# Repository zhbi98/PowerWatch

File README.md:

# PowerWatch 迷你 USB 电源功率计

## 1. 项目简介

PowerWatch 是我设计的一个 Mini-USB 电源功率计，设计包含外观结构，电路 PCB，程序固件。

PowerWatch 在硬件设计上支持同时采样被测电源的电压，电流及功率等参数，同时通过软件的形式实现了电能实时监测功能。

电能实时监测功能可以方便的知道被监测电源所输出的电能。 比如通过 PowerWatch 可以知道充电宝为手机充电时，充电宝流入手机的电能为多少 mAh。

而其中 mAh 表明的是电能单位，例如以 $x$ mA 电流持续输出 $1$ h 时间，则输出的电能为 $x$ mAh。

## 2. 硬件介绍

**(1)** 微控制器：采用国产兆易 GD32F103RCT6，芯片主频 96MHz 最高可达 108MHz，64P 引脚，RAM 空间 64KB，ROM 空间 256KB，支持 USB 通信。

**(2)** 屏幕：驱动芯片 ST7789V3，材质 IPS，采用 8 位并行 8080 通信接口，分辨率 320x170。

**(3)** Flash 芯片：GD25Q64 64MBit 即 8MByte。

**(4)** 电压电流采样芯片：采用德州仪器 TI 的 INA226AIDGSR 芯片。 

**(5)** 外壳模型：3D 打印，材料使用尼龙或工程塑料 。

## 3. 目录说明

### 3.1 Firmware 目录

该目录包含 PowerWatch 的所有功能源码实现，芯片驱动库，以及 Keil 编译工程所在目录，现在来简单介绍一下。

`mdk5/` 目录即为 MDK-ARM（即 Keil5 集成开发环境） 的工程文件。

`test/` 目录包含所有功能实现源码，以及需要用到的芯片驱动库，图形界面库 LVGL。

程序主要包含以下内容：

**(1)** GD32f103 的 USB Device 设备驱动，USB 驱动使用的设备描述符是 CDC 虚拟串口，使用 USB 接口可以用于和上位机进行数据通讯。

**(2)** ST7789V3 屏幕芯片驱动。

**(3)** 电压电流采样芯片驱动。

**(4)** 移植好的 LVGL8.2.0 的 UI 绘图库，这个 UI 库可以实现美观的图形界面，使用 LVGL 后就不需要我们自己控制屏幕逐像素的绘制图形来实现 UI 了。

注意：如果需要编译此工程需要安装 keil5 集成开发环境，以及在 keil5 中安装 GD32F10 系列的芯片描述包, 安装好后点击本项目工程文件夹下的工程文件启动 keil 直接编译即可。

GD32F10 芯片描述包可以到兆易官方网站下载，找到 **GD32F1x0 AddOn** 压缩包，芯片描述包就在该压缩包下，下载地址：[点击这里](https://www.gd32mcu.com/cn/download/7?kw=GD32F1)。

---

power_watch_firmware_v1.0.hex：为 PowerWatch 源码的编译后的固件，如果使用编译固件，需要使芯片进入 BOOT 模式，并使用 PCB 板上预留的串口来写入该固件。

### 3.2 Hardware 目录

PowerWatch 的 PCB 工程源文件，该文件夹下包含电路原理图，以及 PCB 制造文件（即 Gerber 文件），器件 BOM 单（用于 SMT 贴片），器件位置文件（用于 SMT 贴片）。

将 Gerber 文件压缩后到嘉立创网站下单即可将 PCB 打样出来，BOM 单和器件位置文件是嘉立创格式，PCB 打样后可以自行按照 BOM 单购买元器件手工焊接，或利用我提供的 BOM 单和器件坐标文件运用嘉立创的 SMT 贴片服务来贴片。

硬件 PCB 已经打样验证通过，想制作的小伙伴可以放心打样使用。

---

PCB 设计时原本的设想是使用 **STM32F103RCT6** 这颗芯片作为微控制器使用的，但是奈何 **STM32F103RCT6** 价格较高，所以最终芯片使用的是国产兆易的 **GD32F103RCT6** 系列芯片。

但是这对电路并不影响，因为 **GD32F103RCT6** 可以不需要任何改动而实现 PIN 对 PIN 的引脚以及外设兼容 **STM32F103RCT6** 芯片（即它们的每一根引脚和外设的功能是相同的）。

### 3.3 Image 目录

该目录是功率计制作实物效果图片展示，观看制作效果可以查看该目录下的实物照片。

### 3.4 Structure 目录

该目录存放功率计外壳模型文件 `.step` 格式，外壳模型包含壳体，按键帽，屏幕支架，上盖板，直接下载用于 3D 打印即可。

为了美观考虑盖板最好使用透明亚克力板进行制作，普通 3D 打印无法实现透明。

**(1)** 壳体 box_v2.0.step 建议采用黑色尼龙材材料 3D 打印。

**(2)** 屏幕支架 bracket_v2.0.step 建议采用透明树脂材料 3D 打印。

**(3)** 上盖板 panel_v2.0.step 建议采用亚克力或聚碳酸酯材料 CNC 加工。

**(4)** 按键帽 button1_v2.0.step，button2_v2.0.step，button3_v2.0.step，button4_v2.0.step 建议采用尼龙材料 3D 打印。

### 3.5 Docs 目录

用到的芯片配套的数据手册。

## 4. 外观设计

**最初的 V1.0 版本模型效果**

**改进后 V2.0 版本模型效果**

## 5. 实物展示

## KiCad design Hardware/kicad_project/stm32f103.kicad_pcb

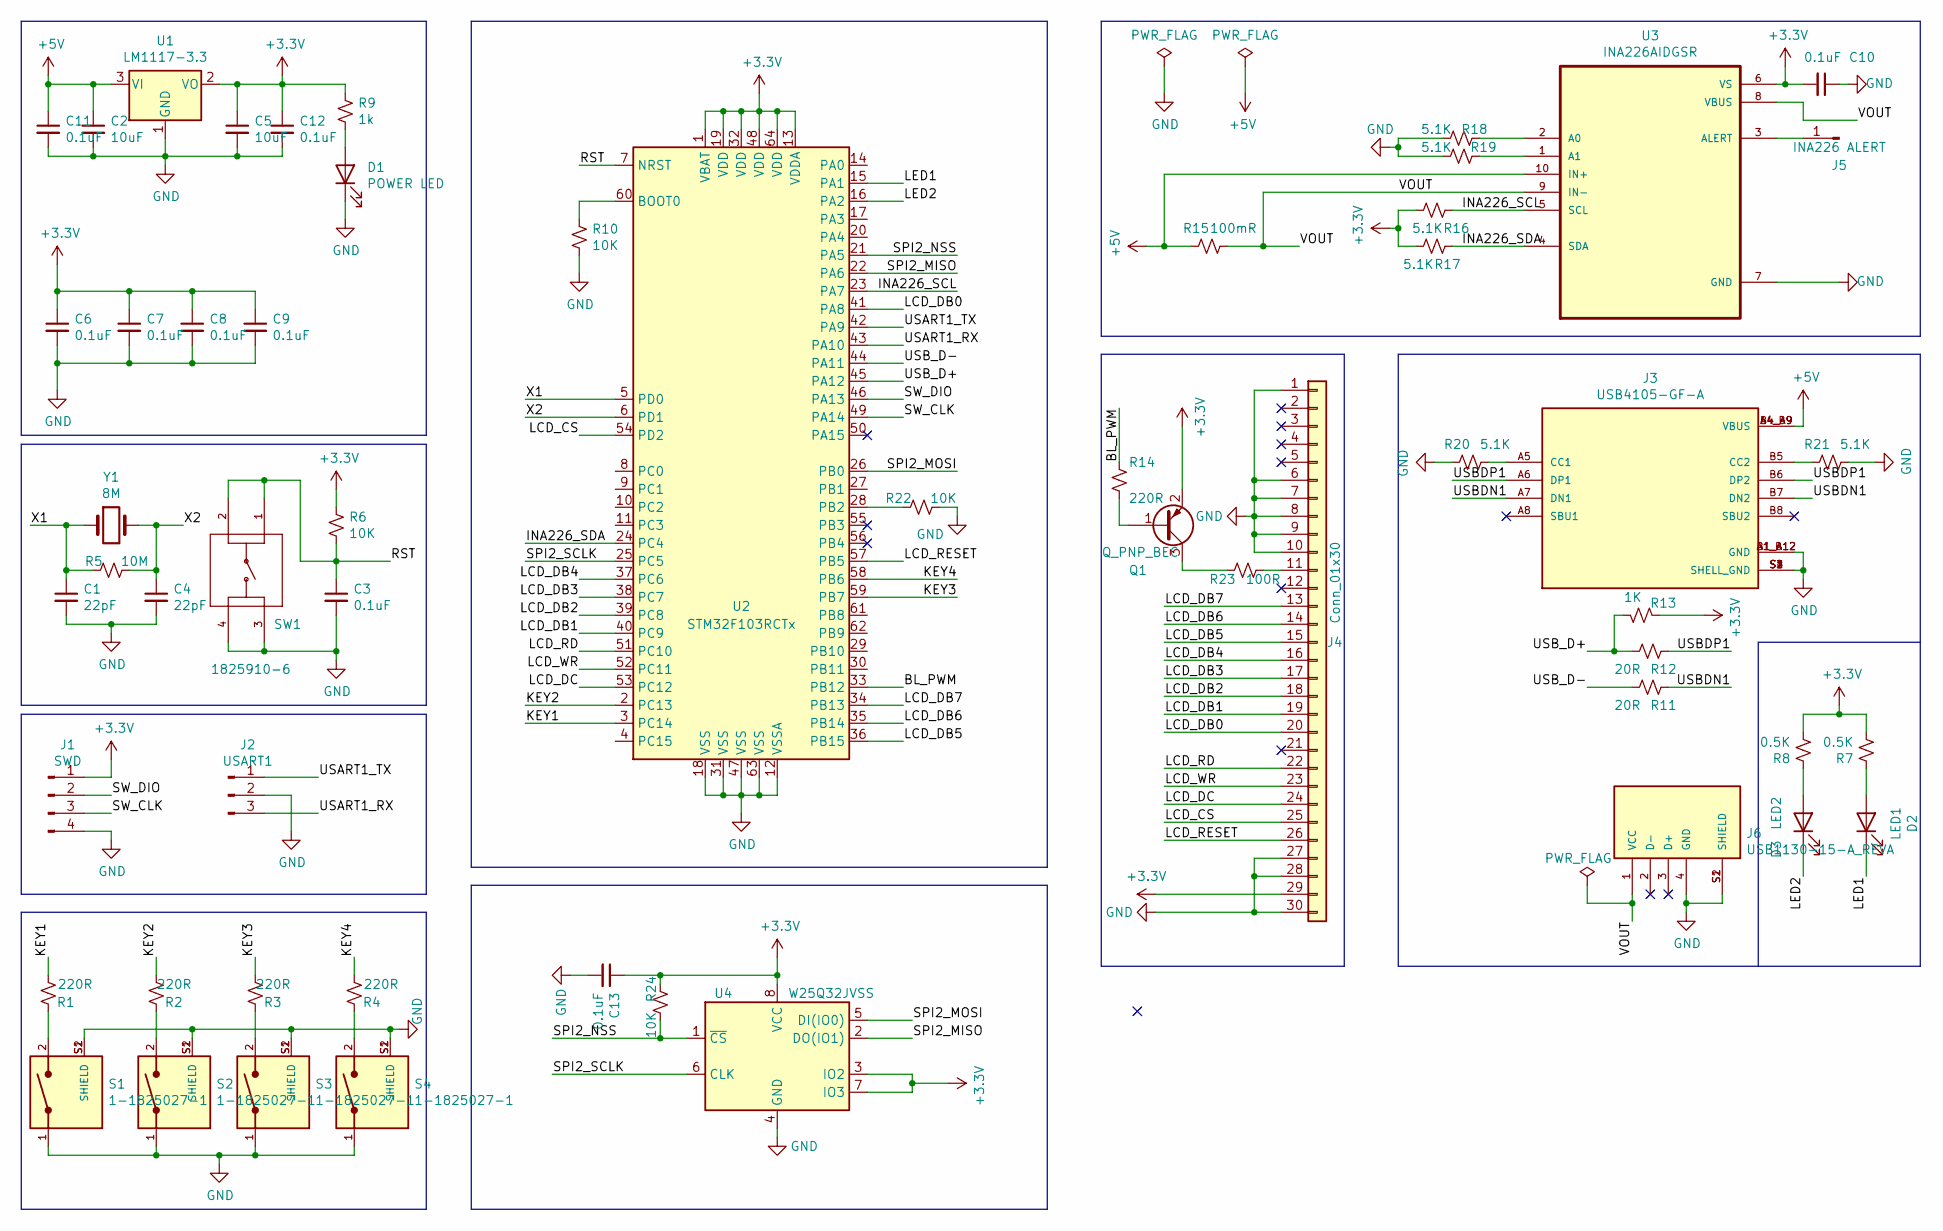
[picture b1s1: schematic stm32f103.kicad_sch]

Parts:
C1, C4: 22pF; C_0805_2012Metric
C2, C5: 10uF; C_0805_2012Metric
C3, C6, C7, C8, C9, C10, C11, C12, C13: 0.1uF; C_0805_2012Metric
D1: POWER LED; LED_0805_2012Metric
D2: LED1; LED_0805_2012Metric
D3: LED2; LED_0805_2012Metric
J1: SWD; PinSocket_1x04_P2.54mm_Vertical
J2: USART1; PinSocket_1x03_P2.54mm_Vertical
J3: USB4105-GF-A; USB-C-SMD_16P_USB4105-GF-A; PARTREV A3
J4: Conn_01x30; Hirose_FH12-30S-0.5SH_1x30-1MP_P0.50mm_Horizontal
J5: INA226 ALERT; PinSocket_1x01_P2.54mm_Vertical
J6: USB1130-15-A_REVA; USB-A-TH_4P_USB1130-15-A-REVA; PARTREV A
Q1: Q_PNP_BEC; SOT-23
R1, R2, R3, R4, R14: 220R; R_0805_2012Metric
R5: 10M; R_0805_2012Metric
R6, R10, R22, R24: 10K; R_0805_2012Metric
R7, R8: 0.5K; R_0805_2012Metric
R9: 1k; R_0805_2012Metric
R11, R12: 20R; R_0805_2012Metric
R13: 1K; R_0805_2012Metric
R15: 100mR; R_2010_5025Metric
R16, R17, R18, R19, R20, R21: 5.1K; R_0805_2012Metric
R23: 100R; R_0805_2012Metric
S1, S2, S3, S4: 1-1825027-1; KEY-TH_L6.0-W6.0-H_B3F-3100
SW1: 1825910-6; KEY-TH_L6.0-W6.0-V_B3F-1000
U1: LM1117-3.3; SOT-223
U2: STM32F103RCTx; LQFP-64_10x10mm_P0.5mm
U3: INA226AIDGSR; VSSOP-10_L2.9-W5.05-P0.5_INA226AIDGSR
U4: W25Q32JVSS; SOIC-8_L4.8-W5.8-P1.27_W25Q32JVSS
Y1: 8M; Crystal_SMD_HC49-SD

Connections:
+3V3: C5.1, C6.1, C7.1, C8.1, C9.1, C10.2, C12.1, C13.1, J1.1, J4.29, Q1.2 (E), R6.1, R7.2, R8.2, R9.1, R13.1, R16.1, R17.1, R24.2, U1.2 (VO), U2.1 (VBAT), U2.13 (VDDA), U2.19 (VDD), U2.32 (VDD), U2.48 (VDD), U2.64 (VDD), U3.6 (VS), U4.3 (IO2), U4.7 (IO3), U4.8 (VCC)
+5V: C2.1, C11.1, J3.A4_B9 (VBUS), J3.B4_A9 (VBUS), R15.2, U1.3 (VI), U3.10 (IN+)
/BL_PWM: R14.1, U2.33 (PB12)
/INA226_SCL: R16.2, U2.23 (PA7), U3.5 (SCL)
/INA226_SDA: R17.2, U2.24 (PC4), U3.4 (SDA)
/KEY1: R1.2, U2.3 (PC14)
/KEY2: R2.2, U2.2 (PC13)
/KEY3: R3.2, U2.59 (PB7)
/KEY4: R4.2, U2.58 (PB6)
/LCD_CS: J4.25, U2.54 (PD2)
/LCD_DB0: J4.20, U2.41 (PA8)
/LCD_DB1: J4.19, U2.40 (PC9)
/LCD_DB2: J4.18, U2.39 (PC8)
/LCD_DB3: J4.17, U2.38 (PC7)
/LCD_DB4: J4.16, U2.37 (PC6)
/LCD_DB5: J4.15, U2.36 (PB15)
/LCD_DB6: J4.14, U2.35 (PB14)
/LCD_DB7: J4.13, U2.34 (PB13)
/LCD_DC: J4.24, U2.53 (PC12)
/LCD_RD: J4.22, U2.51 (PC10)
/LCD_RESET: J4.26, U2.57 (PB5)
/LCD_WR: J4.23, U2.52 (PC11)
/LED1: D2.1 (K), U2.15 (PA1)
/LED2: D3.1 (K), U2.16 (PA2)
/RST: C3.1, R6.2, SW1.1, SW1.2, U2.7 (NRST)
/SPI2_MISO: U2.22 (PA6), U4.2 (DO(IO1))
/SPI2_MOSI: U2.26 (PB0), U4.5 (DI(IO0))
/SPI2_NSS: R24.1, U2.21 (PA5), U4.1 (~CS)
/SPI2_SCLK: U2.25 (PC5), U4.6 (CLK)
/SW_CLK: J1.3, U2.49 (PA14)
/SW_DIO: J1.2, U2.46 (PA13)
/USART1_RX: J2.3, U2.43 (PA10)
/USART1_TX: J2.1, U2.42 (PA9)
/USBDN1: J3.A7 (DN1), J3.B7 (DN2), R11.2
/USBDP1: J3.A6 (DP1), J3.B6 (DP2), R12.2
/USB_D+: R12.1, R13.2, U2.45 (PA12)
/USB_D-: R11.1, U2.44 (PA11)
/VOUT: J6.1 (VCC), R15.1, U3.8 (VBUS), U3.9 (IN-)
/X1: C1.1, R5.2, U2.5 (PD0), Y1.1
/X2: C4.1, R5.1, U2.6 (PD1), Y1.2
GND: C1.2, C2.2, C3.2, C4.2, C5.2, C6.2, C7.2, C8.2, C9.2, C10.1, C11.2, C12.2, C13.2, D1.1 (K), J1.4, J2.2, J3.A1_B12 (GND), J3.B1_A12 (GND), J3.S1 (SHELL_GND), J3.S2 (SHELL_GND), J3.S3 (SHELL_GND), J3.S4 (SHELL_GND), J4.1, J4.6, J4.7, J4.8, J4.9, J4.10, J4.27, J4.28, J4.30, J6.4 (GND), J6.S1 (SHIELD), J6.S2 (SHIELD), R10.2, R18.1, R19.1, R20.2, R21.1, R22.2, S1.1, S1.S1 (SHIELD), S1.S2 (SHIELD), S2.1, S2.S1 (SHIELD), S2.S2 (SHIELD), S3.1, S3.S1 (SHIELD), S3.S2 (SHIELD), S4.1, S4.S1 (SHIELD), S4.S2 (SHIELD), SW1.3, SW1.4, U1.1 (GND), U2.12 (VSSA), U2.18 (VSS), U2.31 (VSS), U2.47 (VSS), U2.63 (VSS), U3.7 (GND), U4.4 (GND)
unnamed: D1.2 (A), R9.2
unnamed: D2.2 (A), R7.1
unnamed: D3.2 (A), R8.1
unnamed: J3.A5 (CC1), R20.1
unnamed: J3.B5 (CC2), R21.2
unnamed: J4.11, R23.2
unnamed: J5.1, U3.3 (ALERT)
unnamed: Q1.1 (B), R14.2
unnamed: Q1.3 (C), R23.1
unnamed: R1.1, S1.2
unnamed: R2.1, S2.2
unnamed: R3.1, S3.2
unnamed: R4.1, S4.2
unnamed: R10.1, U2.60 (BOOT0)
unnamed: R18.2, U3.2 (A0)
unnamed: R19.2, U3.1 (A1)
unnamed: R22.1, U2.28 (PB2)

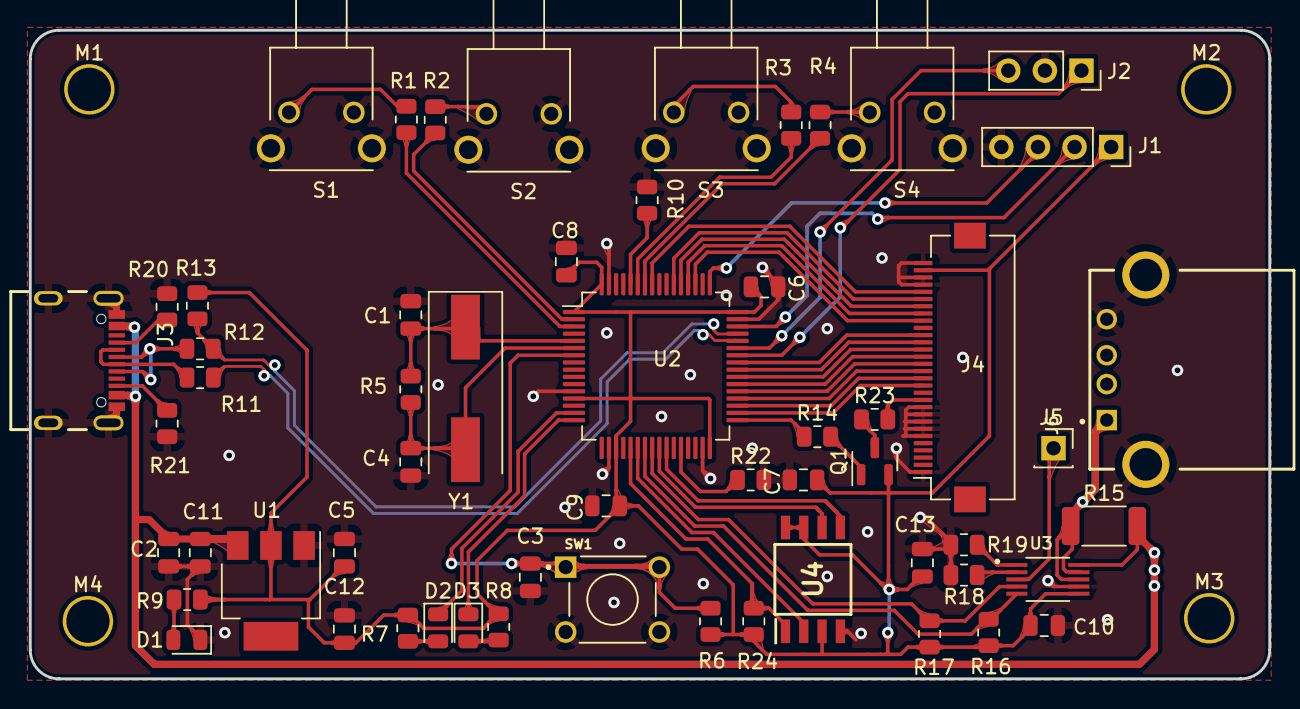
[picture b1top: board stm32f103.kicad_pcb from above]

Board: 2 copper layers, 86.0 x 45.0 mm, 61 parts (0 on the bottom side), 58 nets.

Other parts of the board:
M1, M2, M3, M4: Mounting_Holes_3mm_THT

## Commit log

2022-05-13 remove gd32f303
2022-05-14 add image
2022-05-14 update image
2022-05-14 ina226 fix current and power CAL value
2022-05-14 finx image size
2022-05-18 Rename
2022-05-26 fix pcb router
2022-05-26 add components library
2022-05-26 modify gitignore file, allow submission of .lib files
2022-05-26 Hardware v2.0 gpio remap
2022-05-28 Add ips screen lcd driver
2022-05-28 Fix screen direction describe
2022-05-28 Add gd25q64 flash driver
2022-05-29 Fix GD25Q64 Flash API
2022-05-29 Add lvgl libraries
2022-05-30 Fix st7789v3 video memory coordinate calculation bug
2022-05-30 Modify display driver API
2022-05-31 Add gd32f103 temp sensor
2022-06-01 Add button driver
2022-06-01 Rename file path
2022-06-01 LVGL connect key driver
2022-06-05 Fix sampling resistor
2022-06-06 Add UIKit, UIView
2022-06-07 Add view controller
2022-06-09 Fix UIViewController memory leak problem
2022-06-09 Add Font
2022-06-10 Implement Elecal Dashboards
2022-06-10 UI style design
2022-06-12 Add mAh and mWh
2022-06-13 Modify UIView Controller
2022-06-13 Modify UIView
2022-06-14 Add 3D model
2022-06-14 Modify key event
2022-06-15 Modify power measure
2022-06-15 Update average measure
2022-06-15 Add about view
2022-06-16 Modify about view
2022-06-16 Modify parameter formatting
2022-06-17 Add Elecal schematic
2022-06-18 Support main display switching
2022-06-19 Measurement timing
2022-06-19 Add meas chart
2022-06-21 Split task
2022-06-21 remove test code
2022-06-22 Modify measure part
2022-06-23 Modify ina226 driver, display handler
2022-06-23 Update 3D model
2022-06-25 Update sheet function
2022-06-27 Update 3D models, usb cdc
2022-06-27 Modify data format
2022-06-28 Modify sheet
2022-06-29 Fix negative values are not displayed
2022-07-06 Update LICENSE
2022-07-16 Add firmware
2023-01-04 修改 PCB 工程
2023-01-04 修改目录
2023-01-04 更新 PCB 工程设置
2023-01-10 Update RRADME
2023-02-09 更新 README 以及文件命名
2023-02-23 修改 PCB 库文件
2023-02-23 修改文件组织目录
2023-02-25 更新封装库
2023-02-26 转换符号库文件格式
2023-03-24 Update ina226_i2c.c
    防止编译器优化重要变量
2023-08-17 软件架构调整
2023-08-18 删除中间文件
2023-08-18 目录调整
2023-08-21 Add LocalRPC
2023-08-21 update nt_account
2023-08-22 update main
2023-08-24 框架更新
2023-08-26 修复 NT Action 事件有效位消失问题
2023-08-26 增加卡尔曼滤波
2023-08-27 更新任务管理器
2023-08-27 移除不必要的字体
2023-10-10 修改开关逻辑方式
2023-10-19 修改数据桥接框架
2023-12-15 修改页面调度器，让调度器更加模块化
2023-12-15 修改文件的分类/组织
2025-08-26 重组工程目录便于理解
